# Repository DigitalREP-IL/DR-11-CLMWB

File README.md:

This is a simple breakout board for the Cree CLMWB RGB LED. Onboard resistors are provided to create
approximately equal visible brightness for each channel, with additional jumpers to bypass the resistors
for other current control methods. The simple solder pads are intended to interface directly with bare or
tinned wires.

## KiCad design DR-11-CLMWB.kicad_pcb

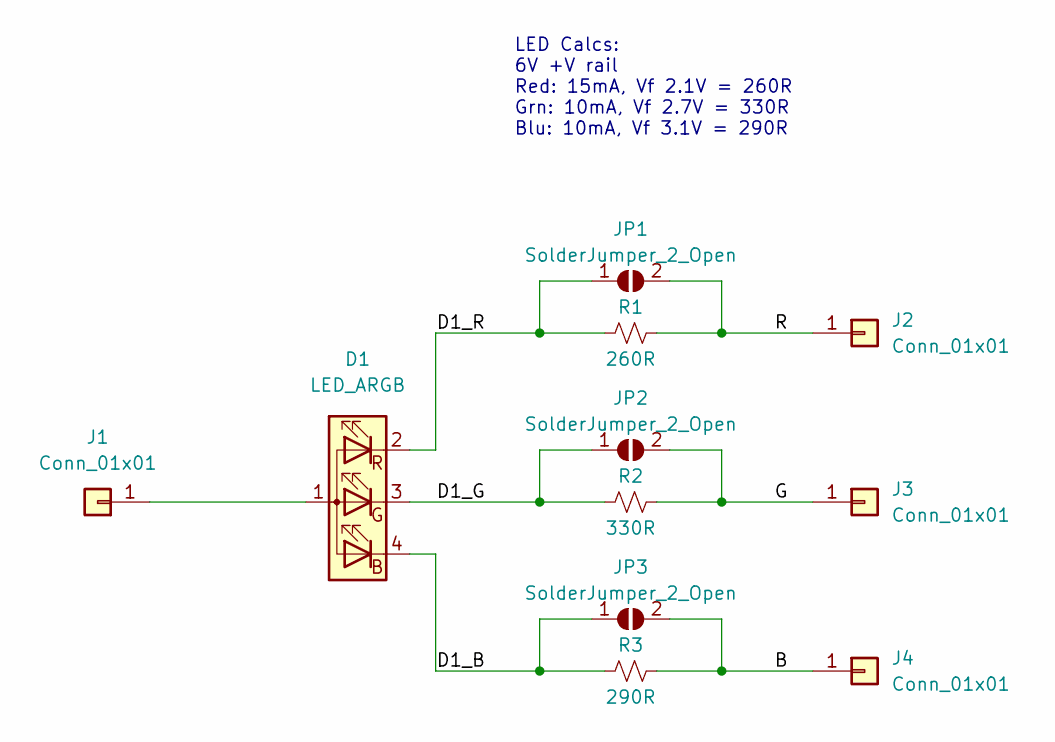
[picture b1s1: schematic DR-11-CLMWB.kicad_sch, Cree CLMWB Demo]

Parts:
D1: LED_ARGB; CLMWB-FKC
J1, J2, J3, J4: Conn_01x01; SolderWirePad_1x01_SMD_1x2mm
JP1, JP2, JP3: SolderJumper_2_Open; SolderJumper-2_P1.3mm_Open_RoundedPad1.0x1.5mm
R1: 260R; R_0603_1608Metric_Pad0.98x0.95mm_HandSolder
R2: 330R; R_0603_1608Metric_Pad0.98x0.95mm_HandSolder
R3: 290R; R_0603_1608Metric_Pad0.98x0.95mm_HandSolder

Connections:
/B: J4.1, JP3.2 (B), R3.2
/D1_B: D1.4 (BK), JP3.1 (A), R3.1
/D1_G: D1.3 (GK), JP2.1 (A), R2.1
/D1_R: D1.2 (RK), JP1.1 (A), R1.1
/G: J3.1, JP2.2 (B), R2.2
/R: J2.1, JP1.2 (B), R1.2
unnamed: D1.1 (A), J1.1

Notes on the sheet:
LED Calcs: 6V +V rail Red: 15mA, Vf 2.1V = 260R Grn: 10mA, Vf 2.7V = 330R Blu: 10mA, Vf 3.1V = 290R

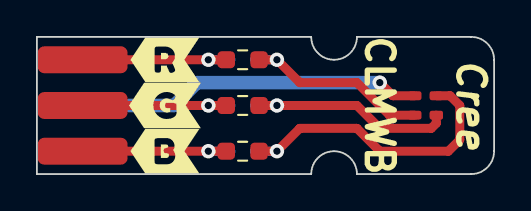
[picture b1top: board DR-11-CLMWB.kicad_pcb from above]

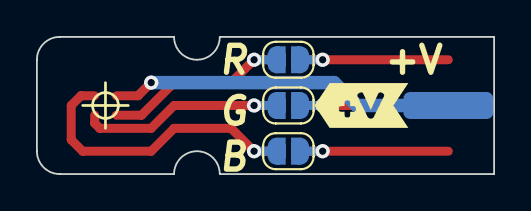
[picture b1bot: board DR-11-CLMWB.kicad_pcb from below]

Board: 2 copper layers, 25.4 x 7.6 mm, 15 parts (5 on the bottom side), 7 nets.

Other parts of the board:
kibuzzard-63977FE2: G***; kibuzzard-63977FE2
kibuzzard-63977FEE: G***; kibuzzard-63977FEE
kibuzzard-63977FFA: G***; kibuzzard-63977FFA
kibuzzard-6397800D: G***; kibuzzard-6397800D
